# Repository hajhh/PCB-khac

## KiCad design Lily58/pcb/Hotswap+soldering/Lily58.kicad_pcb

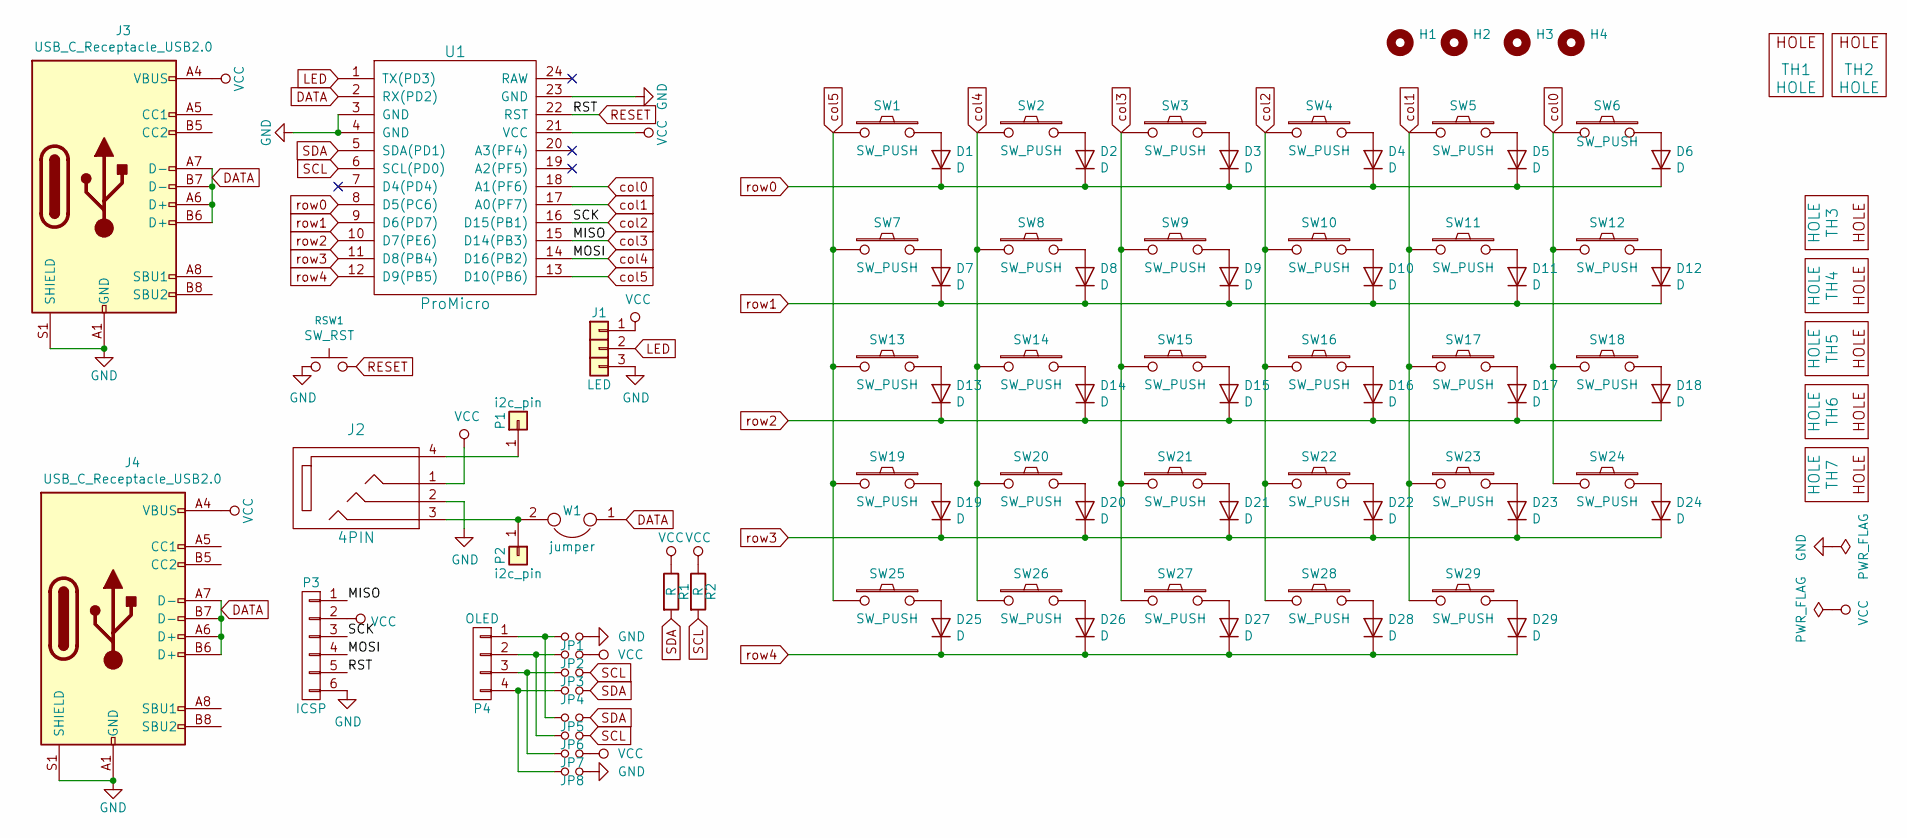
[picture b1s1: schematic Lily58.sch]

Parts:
D1, D2, D3, D4, D5, D6, D7, D8, D9, D10, D11, D12, D13, D14, D15, D16, D17, D18, D19, D20, D21, D22, D23, D24, D25, D26, D27, D28, D29: D; 1N4148_smd
H1, H2: Logo
H3, H4: Logo 2
J1: LED; StripLED
J2: 4PIN; MJ-4PP-9
J3, J4: USB_C_Receptacle_USB2.0; TYPE C
JP1, JP2, JP3, JP4, JP5, JP6, JP7, JP8: Jumper
P1, P2: i2c_pin; 1pin_conn
P3: ICSP
P4: OLED
R1, R2: R; RESISTOR_mini
RSW1: SW_RST; SW_Tactile_SPST_Angled_PTS645Vx39-2LFS
SW1, SW2, SW3, SW4, SW5, SW6, SW7, SW8, SW9, SW10, SW11, SW12, SW13, SW14, SW15, SW16, SW17, SW18, SW19, SW20, SW21, SW22, SW23, SW24, SW25, SW26, SW27, SW28, SW29: SW_PUSH; MX_kien
TH1, TH2: HOLE; HOLE_M2
TH3, TH4, TH5, TH6, TH7: HOLE; HOLE_M2_TH
U1: ProMicro; ProMicro_rev2
W1: jumper; jumper_data

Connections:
DATA: J3.A6 (D+), J3.A7 (D-), J3.B6 (D+), J3.B7 (D-), J4.A6 (D+), J4.A7 (D-), J4.B6 (D+), J4.B7 (D-), U1.2 (RX(PD2)), W1.1
GND: J1.3, J2.2, J3.A1 (GND), J3.A12 (GND), J3.B1 (GND), J3.B12 (GND), J3.S1 (SHIELD), J4.A1 (GND), J4.A12 (GND), J4.B1 (GND), J4.B12 (GND), J4.S1 (SHIELD), JP1.2, JP8.2, P3.6, RSW1.1, U1.3 (GND), U1.4 (GND), U1.23 (GND)
LED: J1.2, U1.1 (TX(PD3))
unnamed: D1.2 (A), SW1.1
unnamed: D2.2 (A), SW2.2
unnamed: D3.2 (A), SW3.2
unnamed: D4.2 (A), SW4.2
unnamed: D5.2 (A), SW5.2
unnamed: D6.2 (A), SW6.2
unnamed: D7.2 (A), SW7.1
unnamed: D8.2 (A), SW8.2
unnamed: D9.2 (A), SW9.2
unnamed: D10.2 (A), SW10.2
unnamed: D11.2 (A), SW11.2
unnamed: D12.2 (A), SW12.2
unnamed: D13.2 (A), SW13.1
unnamed: D14.2 (A), SW14.2
unnamed: D15.2 (A), SW15.2
unnamed: D16.2 (A), SW16.2
unnamed: D17.2 (A), SW17.2
unnamed: D18.2 (A), SW18.2
unnamed: D19.2 (A), SW19.1
unnamed: D20.2 (A), SW20.2
unnamed: D21.2 (A), SW21.2
unnamed: D22.2 (A), SW22.2
unnamed: D23.2 (A), SW23.2
unnamed: D24.2 (A), SW24.2
unnamed: D25.2 (A), SW25.1
unnamed: D26.2 (A), SW26.1
unnamed: D27.2 (A), SW27.2
unnamed: D28.2 (A), SW28.2
unnamed: D29.2 (A), SW29.2
unnamed: J2.3, P2.1, W1.2
unnamed: J2.4, P1.1
unnamed: JP1.1, JP5.1, P4.1
unnamed: JP2.1, JP6.1, P4.2
unnamed: JP3.1, JP7.1, P4.3
unnamed: JP4.1, JP8.1, P4.4
RESET: P3.5, RSW1.2, U1.22 (RST)
SCL: JP3.2, JP6.2, R2.2, U1.6 (SCL(PD0))
SDA: JP4.2, JP5.2, R1.2, U1.5 (SDA(PD1))
VCC: J1.1, J2.1, J3.A4 (VBUS), J3.A9 (VBUS), J3.B4 (VBUS), J3.B9 (VBUS), J4.A4 (VBUS), J4.A9 (VBUS), J4.B4 (VBUS), J4.B9 (VBUS), JP2.2, JP7.2, P3.2, R1.1, R2.1, U1.21 (VCC)
col0: SW6.1, SW12.1, SW18.1, SW24.1, U1.18 (A1(PF6))
col1: SW5.1, SW11.1, SW17.1, SW23.1, SW29.1, U1.17 (A0(PF7))
col2: P3.3, SW4.1, SW10.1, SW16.1, SW22.1, SW28.1, U1.16 (D15(PB1))
col3: P3.1, SW3.1, SW9.1, SW15.1, SW21.1, SW27.1, U1.15 (D14(PB3))
col4: P3.4, SW2.1, SW8.1, SW14.1, SW20.1, SW26.2, U1.14 (D16(PB2))
col5: SW1.2, SW7.2, SW13.2, SW19.2, SW25.2, U1.13 (D10(PB6))
row0: D1.1 (K), D2.1 (K), D3.1 (K), D4.1 (K), D5.1 (K), D6.1 (K), U1.8 (D5(PC6))
row1: D7.1 (K), D8.1 (K), D9.1 (K), D10.1 (K), D11.1 (K), D12.1 (K), U1.9 (D6(PD7))
row2: D13.1 (K), D14.1 (K), D15.1 (K), D16.1 (K), D17.1 (K), D18.1 (K), U1.10 (D7(PE6))
row3: D19.1 (K), D20.1 (K), D21.1 (K), D22.1 (K), D23.1 (K), D24.1 (K), U1.11 (D8(PB4))
row4: D25.1 (K), D26.1 (K), D27.1 (K), D28.1 (K), D29.1 (K), U1.12 (D9(PB5))

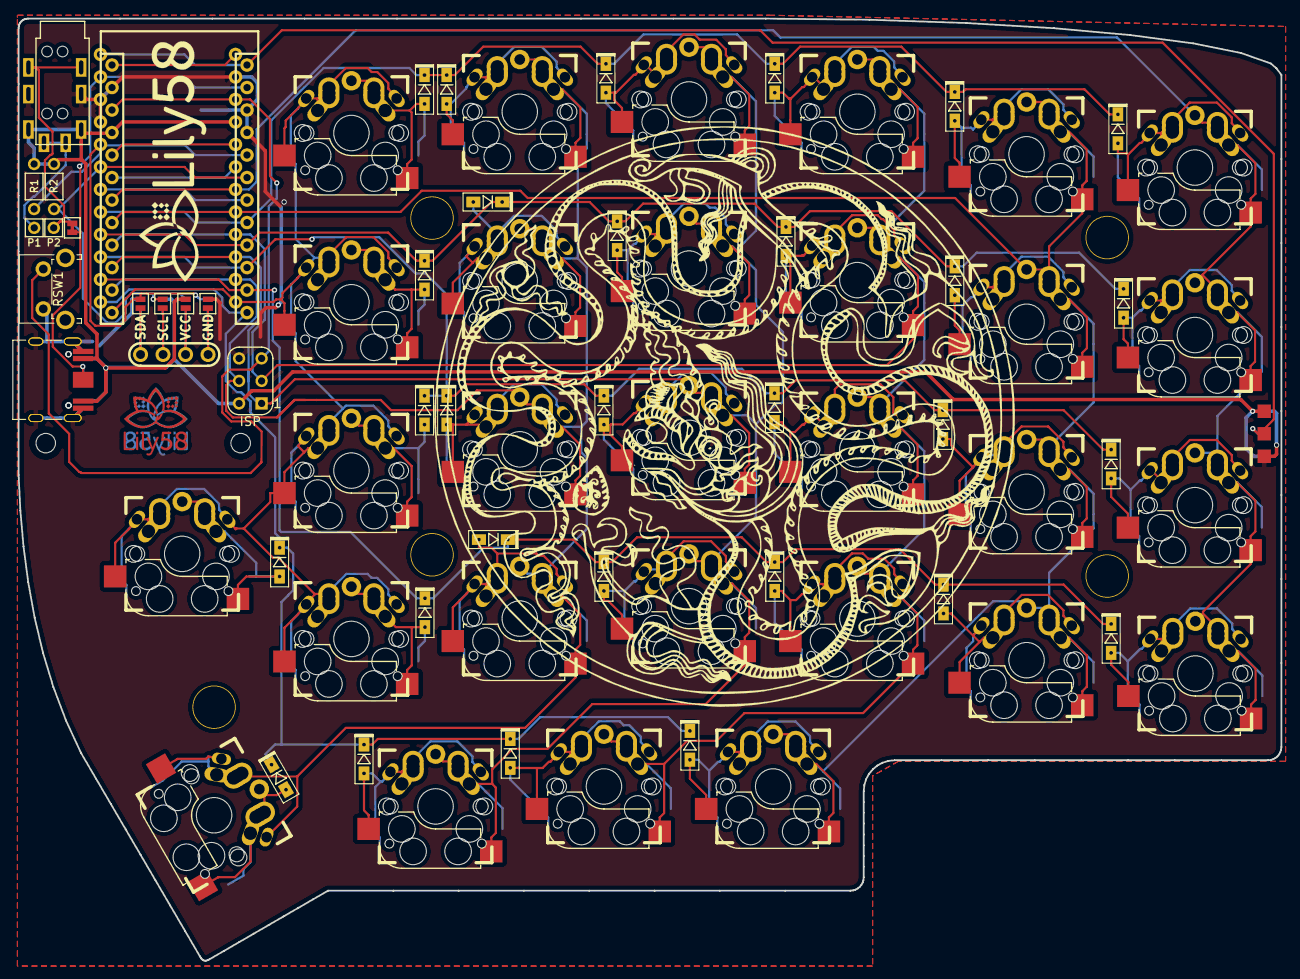
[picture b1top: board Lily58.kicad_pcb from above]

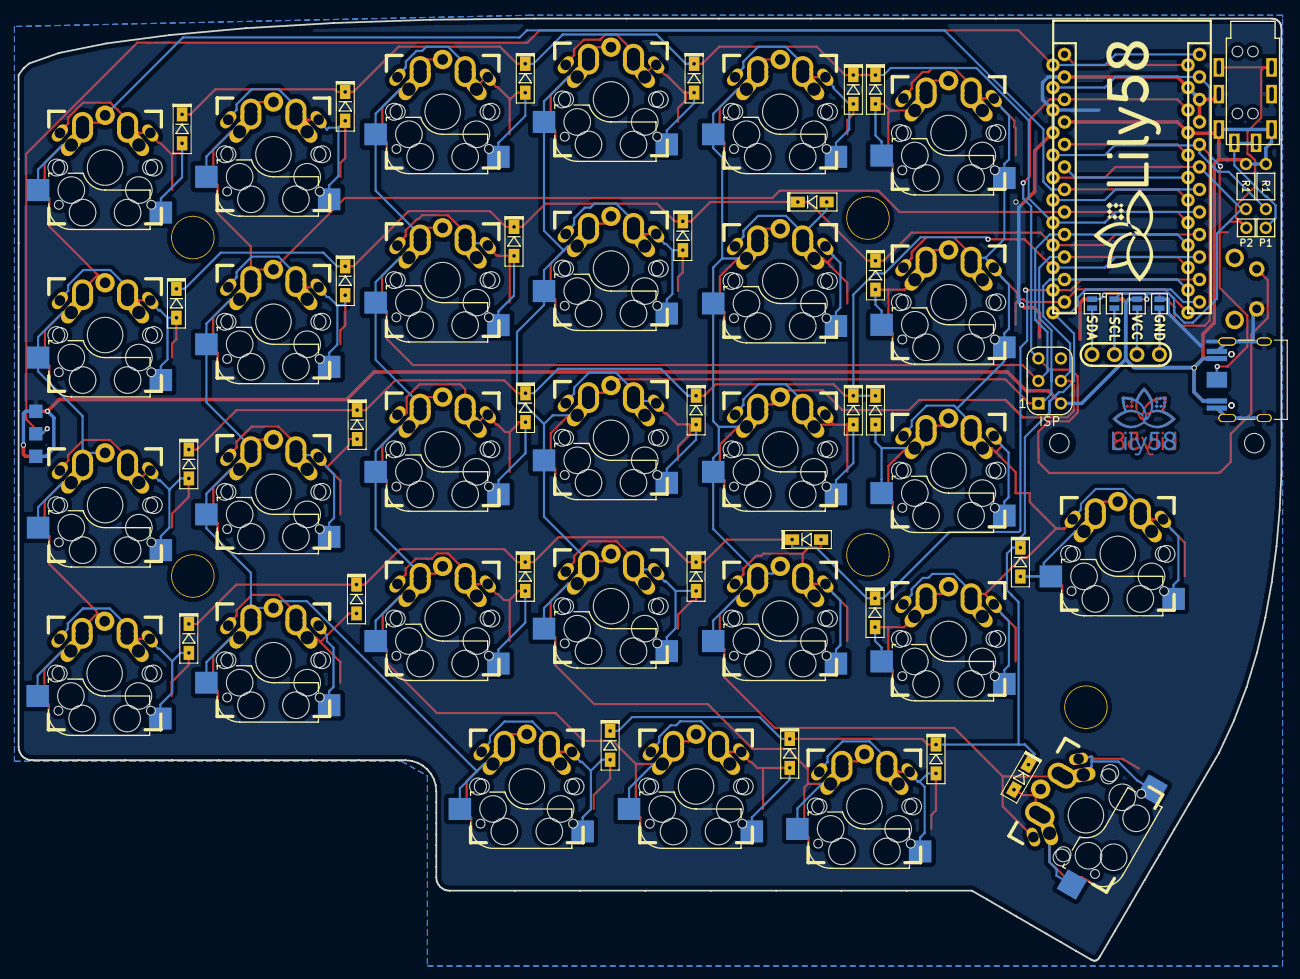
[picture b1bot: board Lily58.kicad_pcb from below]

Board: 2 copper layers, 142.5 x 106.3 mm, 90 parts (7 on the bottom side), 53 nets.

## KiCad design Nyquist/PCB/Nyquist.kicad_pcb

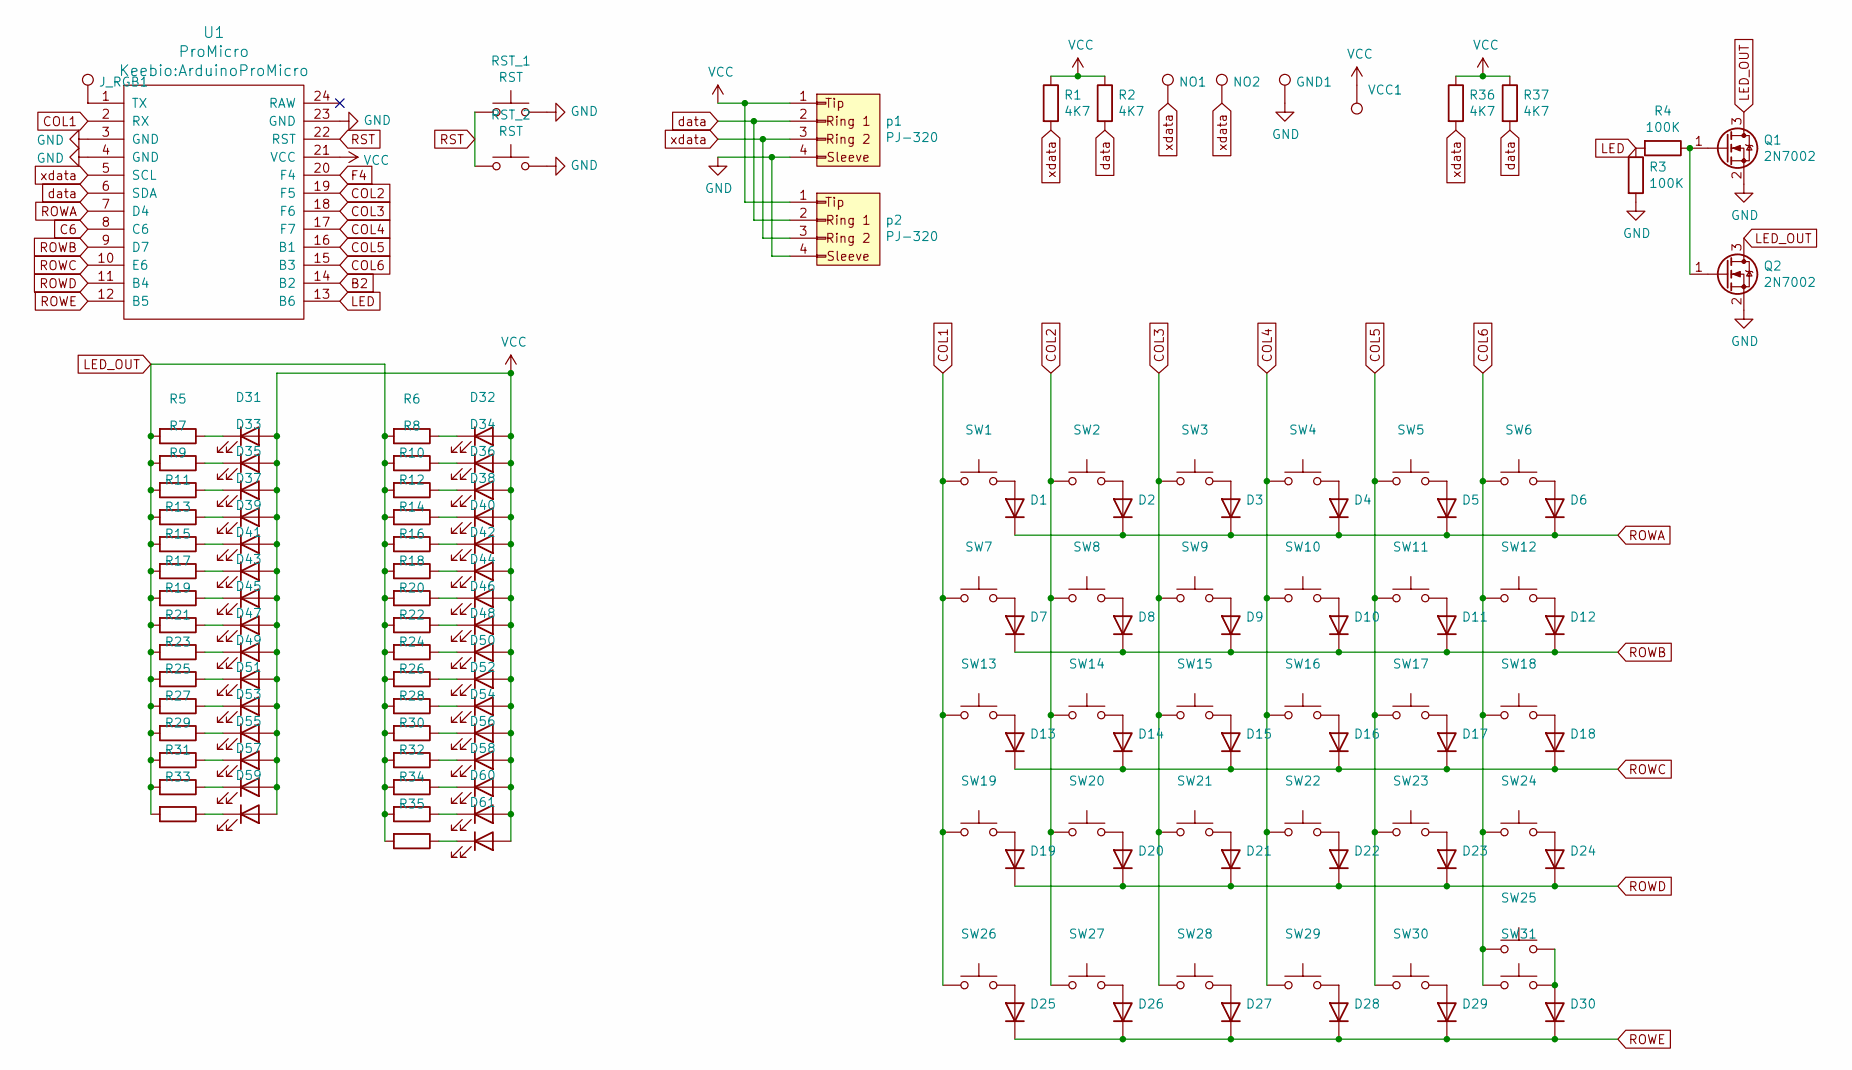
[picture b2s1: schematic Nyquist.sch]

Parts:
D1, D2, D3, D4, D5, D6, D7, D8, D9, D10, D11, D12, D13, D14, D15, D16, D17, D18, D19, D20, D21, D22, D23, D24, D25, D26, D27, D28, D29, D30: Diode
D31, D32, D33, D34, D35, D36, D37, D38, D39, D40, D41, D42, D43, D44, D45, D46, D47, D48, D49, D50, D51, D52, D53, D54, D55, D56, D57, D58, D59, D60, D61: LED_3MM
GND1: TestPoint
J_RGB1: TestPoint
NO1, NO2: TestPoint
Q1, Q2: 2N7002; SOT-23
R1, R2, R36, R37: 4K7; Resistor-Compact
R3, R4: 100K; R
R5, R6, R7, R8, R9, R10, R11, R12, R13, R14, R15, R16, R17, R18, R19, R20, R21, R22, R23, R24, R25, R26, R27, R28, R29, R30, R31, R32, R33, R34, R35: R
RST_1, RST_2: RST
SW1, SW2, SW3, SW4, SW5, SW6, SW7, SW8, SW9, SW10, SW11, SW12, SW13, SW14, SW15, SW16, SW17, SW18, SW19, SW20, SW21, SW22, SW23, SW24, SW25, SW26, SW27, SW28, SW29, SW30: 1u
SW31: 2u
U1: ProMicro; ArduinoProMicro
VCC1: TestPoint
p1, p2: PJ-320; PJ_320

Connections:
B2: U1.14 (B2)
C6: U1.8 (C6)
COL1: SW1.1, SW7.1, SW13.1, SW19.1, SW26.1, U1.2 (RX)
COL2: SW2.1, SW8.1, SW14.1, SW20.1, SW27.1, U1.19 (F5)
COL3: SW3.2, SW9.2, SW15.1, SW21.1, SW28.1, U1.18 (F6)
COL4: SW4.2, SW10.2, SW16.2, SW22.2, SW29.1, U1.17 (F7)
COL5: SW5.2, SW11.2, SW17.2, SW23.2, SW30.1, U1.16 (B1)
COL6: SW6.2, SW12.2, SW18.2, SW24.2, SW25.1, SW31.1, U1.15 (B3)
F4: U1.20 (F4)
GND: GND1.1, Q1.2 (S), Q2.2 (S), R3.2, RST_1.2, RST_2.2, U1.3 (GND), U1.4 (GND), U1.23 (GND), p1.4, p2.4
LED: R3.1, R4.2, U1.13 (B6)
LED_OUT: Q1.3 (D), Q2.3 (D), R5.2, R6.2, R7.2, R8.2, R9.2, R10.2, R11.2, R12.2, R13.2, R14.2, R15.2, R16.2, R17.2, R18.2, R19.2, R20.2, R21.2, R22.2, R23.2, R24.2, R25.2, R26.2, R27.2, R28.2, R29.2, R30.2, R31.2, R32.2, R33.2, R34.2, R35.2
unnamed: D1.1 (A), SW1.2
unnamed: D2.1 (A), SW2.2
unnamed: D3.1 (A), SW3.1
unnamed: D4.1 (A), SW4.1
unnamed: D5.1 (A), SW5.1
unnamed: D6.1 (A), SW6.1
unnamed: D7.1 (A), SW7.2
unnamed: D8.1 (A), SW8.2
unnamed: D9.1 (A), SW9.1
unnamed: D10.1 (A), SW10.1
unnamed: D11.1 (A), SW11.1
unnamed: D12.1 (A), SW12.1
unnamed: D13.1 (A), SW13.2
unnamed: D14.1 (A), SW14.2
unnamed: D15.1 (A), SW15.2
unnamed: D16.1 (A), SW16.1
unnamed: D17.1 (A), SW17.1
unnamed: D18.1 (A), SW18.1
unnamed: D19.1 (A), SW19.2
unnamed: D20.1 (A), SW20.2
unnamed: D21.1 (A), SW21.2
unnamed: D22.1 (A), SW22.1
unnamed: D23.1 (A), SW23.1
unnamed: D24.1 (A), SW24.1
unnamed: D25.1 (A), SW26.2
unnamed: D26.1 (A), SW27.2
unnamed: D27.1 (A), SW28.2
unnamed: D28.1 (A), SW29.2
unnamed: D29.1 (A), SW30.2
unnamed: D30.1 (A), SW25.2, SW31.2
unnamed: D31.1 (K), R5.1
unnamed: D32.1 (K), R6.1
unnamed: D33.1 (K), R7.1
unnamed: D34.1 (K), R8.1
unnamed: D35.1 (K), R9.1
unnamed: D36.1 (K), R10.1
unnamed: D37.1 (K), R11.1
unnamed: D38.1 (K), R12.1
unnamed: D39.1 (K), R13.1
unnamed: D40.1 (K), R14.1
unnamed: D41.1 (K), R15.1
unnamed: D42.1 (K), R16.1
unnamed: D43.1 (K), R17.1
unnamed: D44.1 (K), R18.1
unnamed: D45.1 (K), R19.1
unnamed: D46.1 (K), R20.1
unnamed: D47.1 (K), R21.1
unnamed: D48.1 (K), R22.1
unnamed: D49.1 (K), R23.1
unnamed: D50.1 (K), R24.1
unnamed: D51.1 (K), R25.1
unnamed: D52.1 (K), R26.1
unnamed: D53.1 (K), R27.1
unnamed: D54.1 (K), R28.1
unnamed: D55.1 (K), R29.1
unnamed: D56.1 (K), R30.1
unnamed: D57.1 (K), R31.1
unnamed: D58.1 (K), R32.1
unnamed: D59.1 (K), R33.1
unnamed: D60.1 (K), R34.1
unnamed: D61.1 (K), R35.1
unnamed: J_RGB1.1, U1.1 (TX)
unnamed: Q1.1 (G), Q2.1 (G), R4.1
ROWA: D1.2 (K), D2.2 (K), D3.2 (K), D4.2 (K), D5.2 (K), D6.2 (K), U1.7 (D4)
ROWB: D7.2 (K), D8.2 (K), D9.2 (K), D10.2 (K), D11.2 (K), D12.2 (K), U1.9 (D7)
ROWC: D13.2 (K), D14.2 (K), D15.2 (K), D16.2 (K), D17.2 (K), D18.2 (K), U1.10 (E6)
ROWD: D19.2 (K), D20.2 (K), D21.2 (K), D22.2 (K), D23.2 (K), D24.2 (K), U1.11 (B4)
ROWE: D25.2 (K), D26.2 (K), D27.2 (K), D28.2 (K), D29.2 (K), D30.2 (K), U1.12 (B5)
RST: RST_1.1, RST_2.1, U1.22 (RST)
VCC: D31.2 (A), D32.2 (A), D33.2 (A), D34.2 (A), D35.2 (A), D36.2 (A), D37.2 (A), D38.2 (A), D39.2 (A), D40.2 (A), D41.2 (A), D42.2 (A), D43.2 (A), D44.2 (A), D45.2 (A), D46.2 (A), D47.2 (A), D48.2 (A), D49.2 (A), D50.2 (A), D51.2 (A), D52.2 (A), D53.2 (A), D54.2 (A), D55.2 (A), D56.2 (A), D57.2 (A), D58.2 (A), D59.2 (A), D60.2 (A), D61.2 (A), R1.1, R2.1, R36.1, R37.1, U1.21 (VCC), VCC1.1, p1.1, p2.1
data: R2.2, R37.2, U1.6 (SDA), p1.2, p2.2
xdata: NO1.1, NO2.1, R1.2, R36.2, U1.5 (SCL), p1.3, p2.3

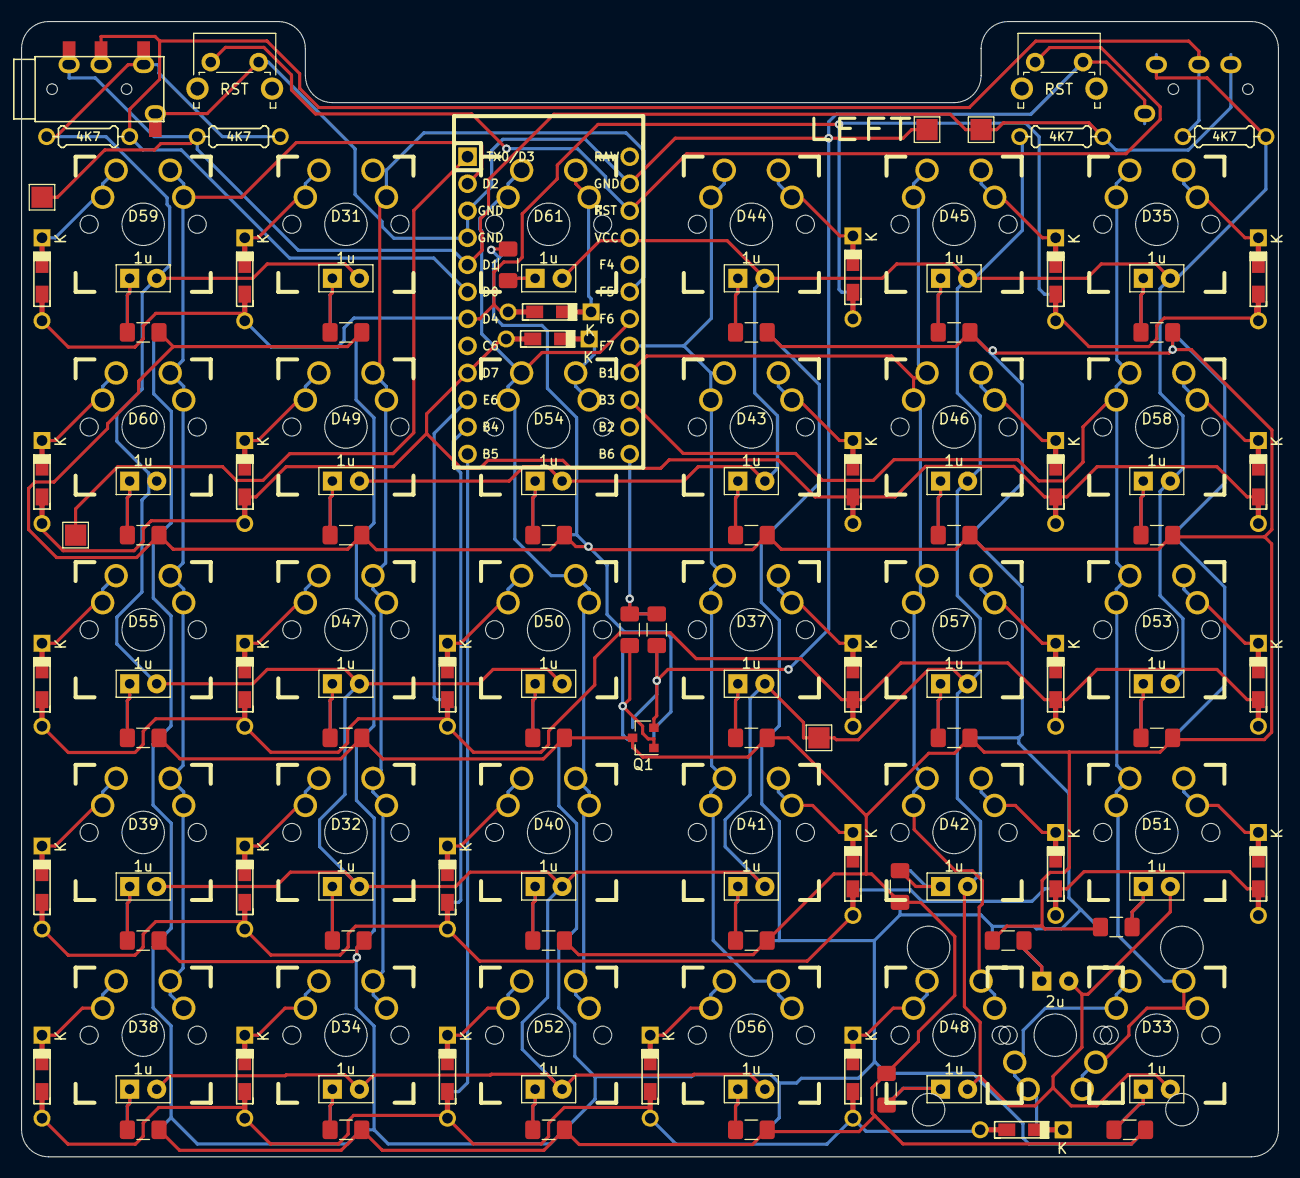
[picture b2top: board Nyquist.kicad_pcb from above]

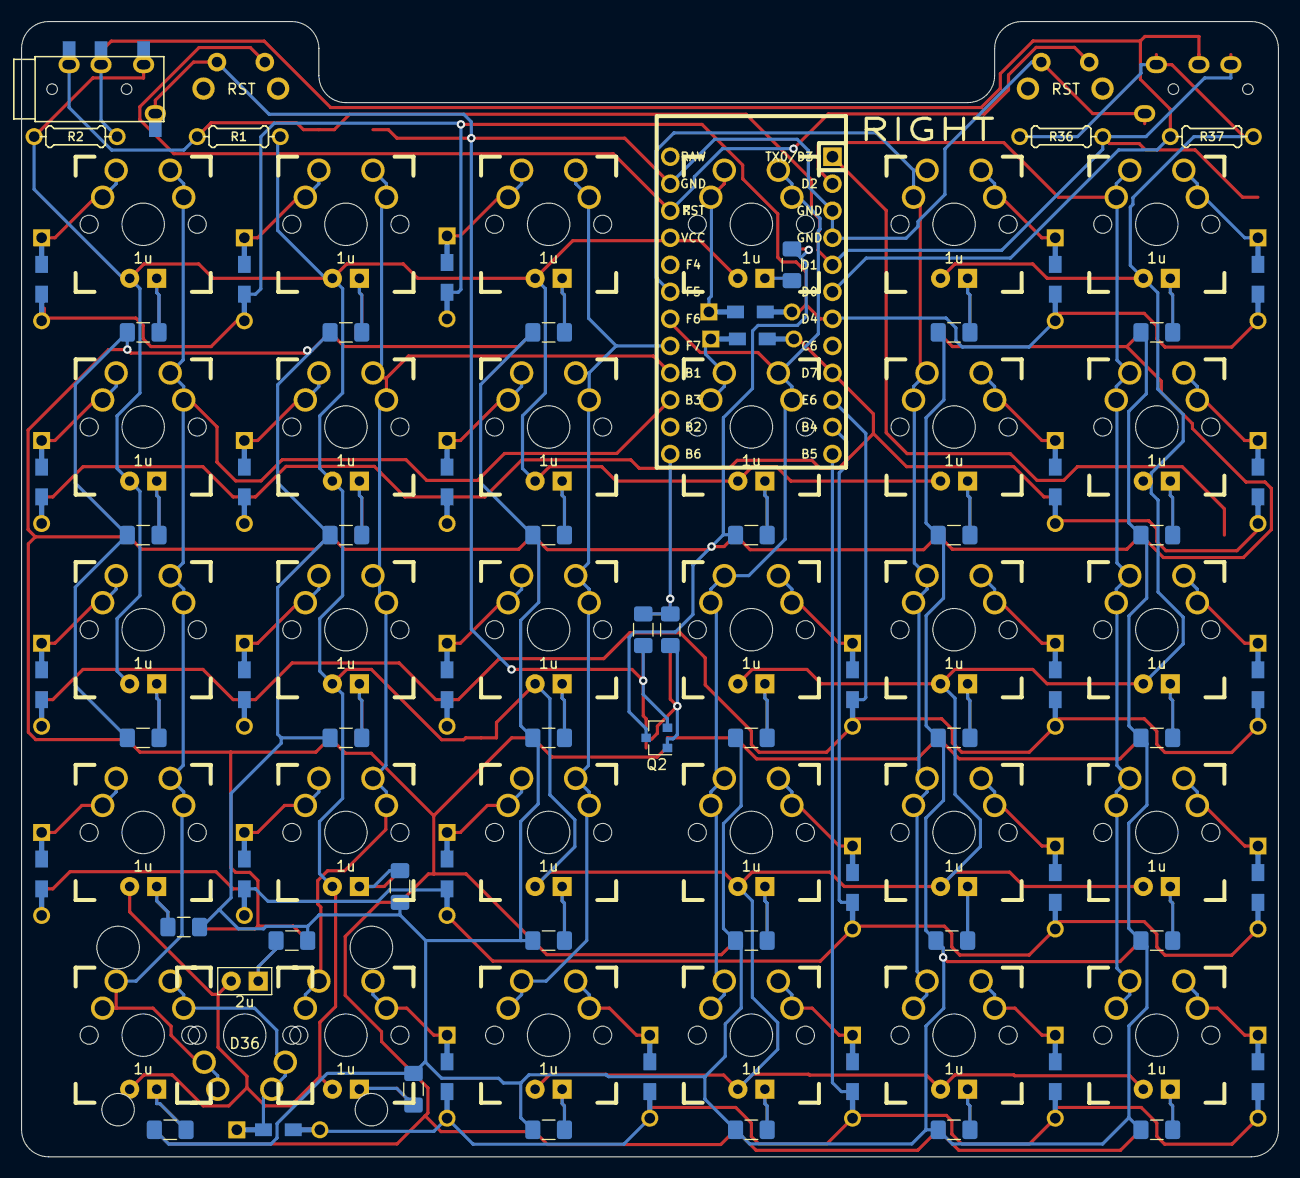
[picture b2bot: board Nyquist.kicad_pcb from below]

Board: 2 copper layers, 118.1 x 106.7 mm, 141 parts (3 on the bottom side), 81 nets.

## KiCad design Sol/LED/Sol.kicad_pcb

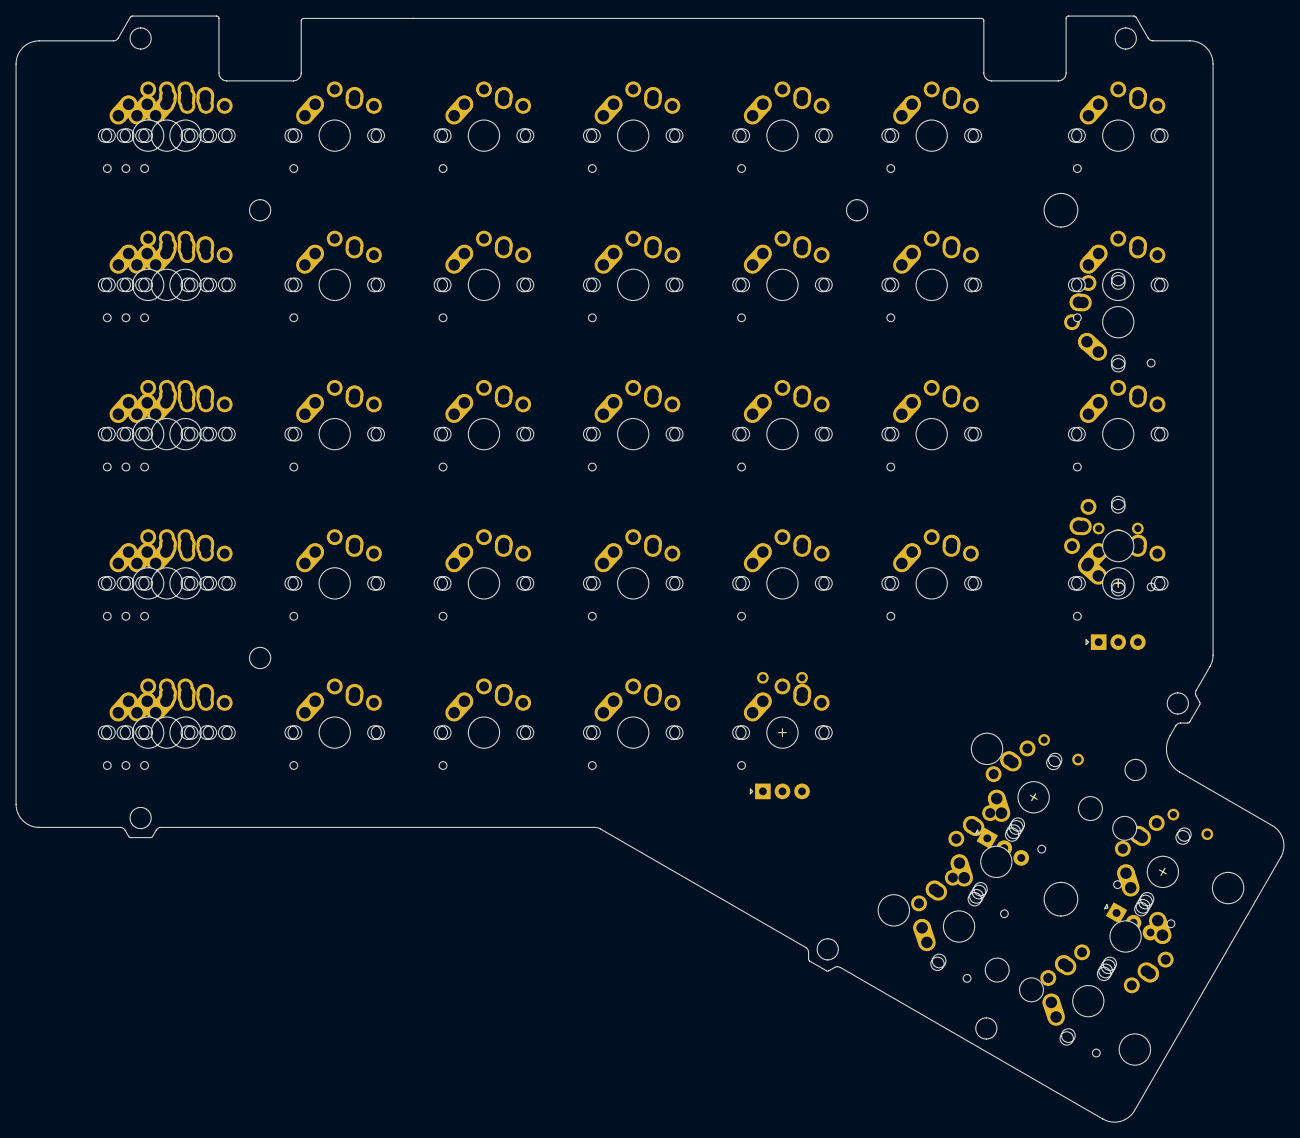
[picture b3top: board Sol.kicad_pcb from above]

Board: 2 copper layers, 161.8 x 141.2 mm, 48 parts (1 on the bottom side), 3 nets, no tracks yet.

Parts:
H1, H2: Stab
SW1, SW8, SW15, SW22, SW29: MX
SW2, SW3, SW4, SW5, SW6, SW7, SW9, SW10, SW11, SW12, SW13, SW14, SW16, SW17, SW18, SW19, SW20, SW21, SW23, SW24, SW25, SW26, SW27, SW28, SW30, SW31, SW32, SW33, SW34, SW35, SW36, SW37, SW38, SW39, SW40, SW41: MX-1U-NoLED
SW42, SW43, SW44, SW45: Econder
U1: ATmega32U4-MU; QFN-44-1EP_7x7mm_P0.5mm_EP5.2x5.2mm

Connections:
unnamed: U1.14, U1.34
unnamed: U1.15, U1.23, U1.35, U1.43, U1.45
unnamed: U1.24, U1.44

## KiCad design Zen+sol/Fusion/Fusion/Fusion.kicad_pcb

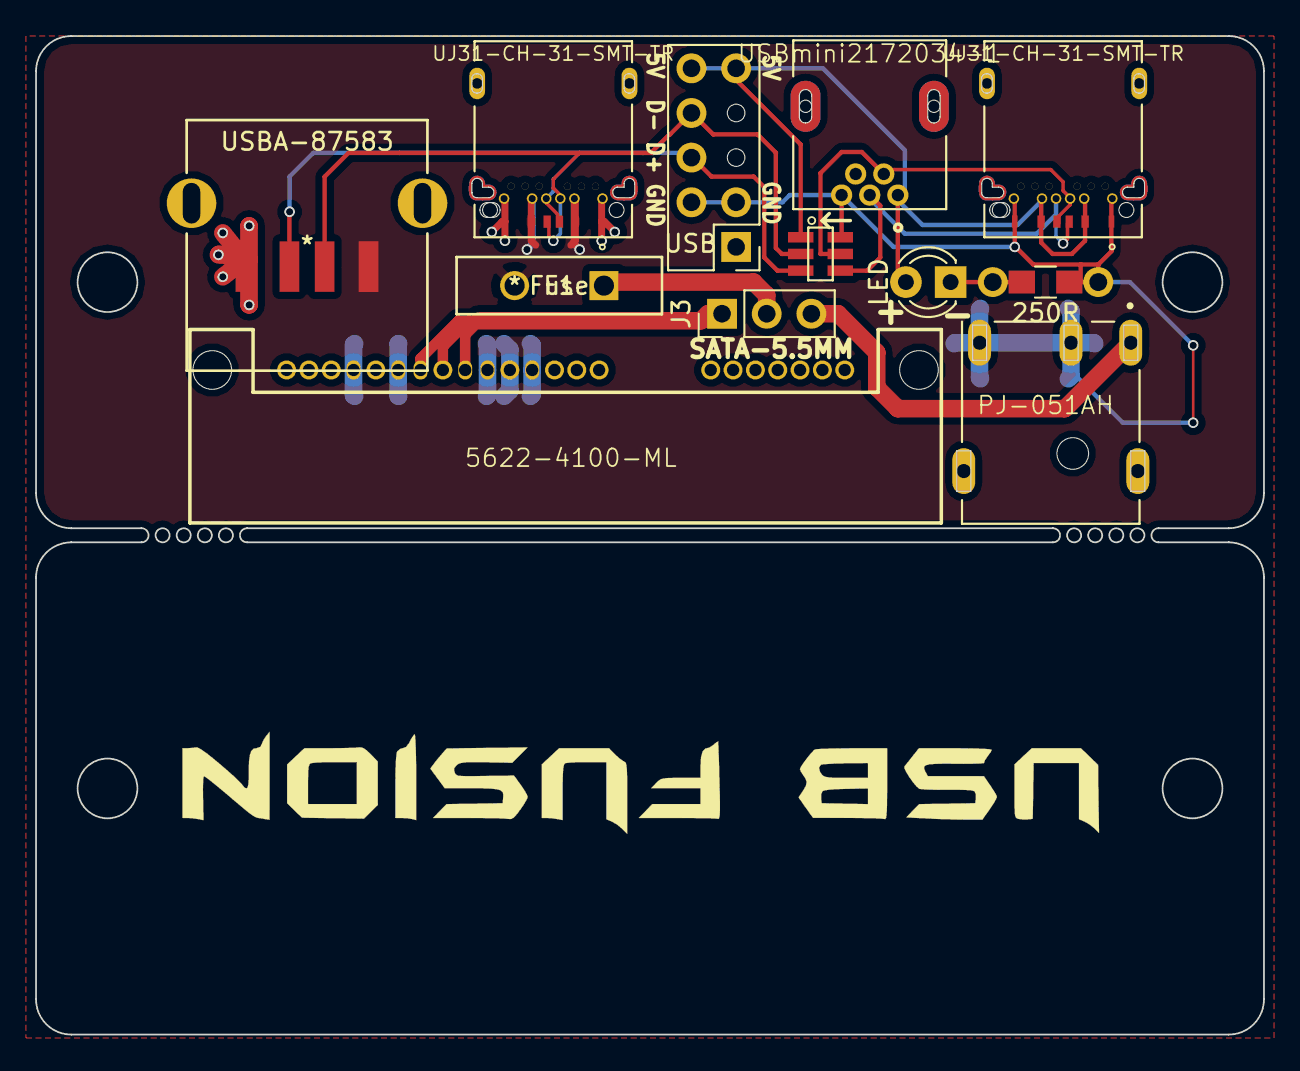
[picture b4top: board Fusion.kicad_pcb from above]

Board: 2 copper layers, 69.8 x 56.8 mm, 12 parts (0 on the bottom side), 11 nets.

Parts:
D1: LED; LED_D3.0mm
F1: Fuse; RUEF300
J1: USBmini2172034-1; TE_2172034-1
J2, J5: UJ31-CH-31-SMT-TR; CUI_UJ31-CH-31-SMT-TR
J3: Conn_01x03_Male; Pin_Header_Straight_1x03_Pitch2.54mm
J4: USBA-87583; 87583-2010BLF
J6: PJ-051AH; CUI_PJ-051AH
P1: 5622-4100-ML; 3M_5622-4100-ML
R1: 250R; R_0805_HandSoldering
U1: STF202-22T1G
USB: 2x05_2.54mm; Pin_Header_Straight_2x05_Pitch2.54mm

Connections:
+5V: F1.2, J2.A4, J2.A9, J2.B4, J2.B9, J4.1
/D+: J1.3, J2.A6, J2.B6, J4.3, J5.A6, J5.B6, U1.3, U1.4, USB.6
/D-: J1.2, J2.A7, J2.B7, J4.2, J5.A7, J5.B7, U1.2, U1.5
/USBGND: J1.5, J1.SH1, J1.SH2, J5.A1, J5.A12, J5.B1, J5.B12, J5.EXPB, R1.2, U1.6
/USBVCC: D1.2, J1.1, J5.A4, J5.A9, J5.B4, J5.B9, U1.1, USB.9
GND: J2.A1, J2.A12, J2.B1, J2.B12, J2.EXPB, J4.4, J6.2, J6.3, P1.P4, P1.P5, P1.P6, P1.P10, P1.P12
unnamed: D1.1, R1.1
unnamed: F1.1, J3.2
unnamed: J3.1, P1.P7, P1.P8, P1.P9
unnamed: J3.3, J6.1
unnamed: J6.5, J6.6

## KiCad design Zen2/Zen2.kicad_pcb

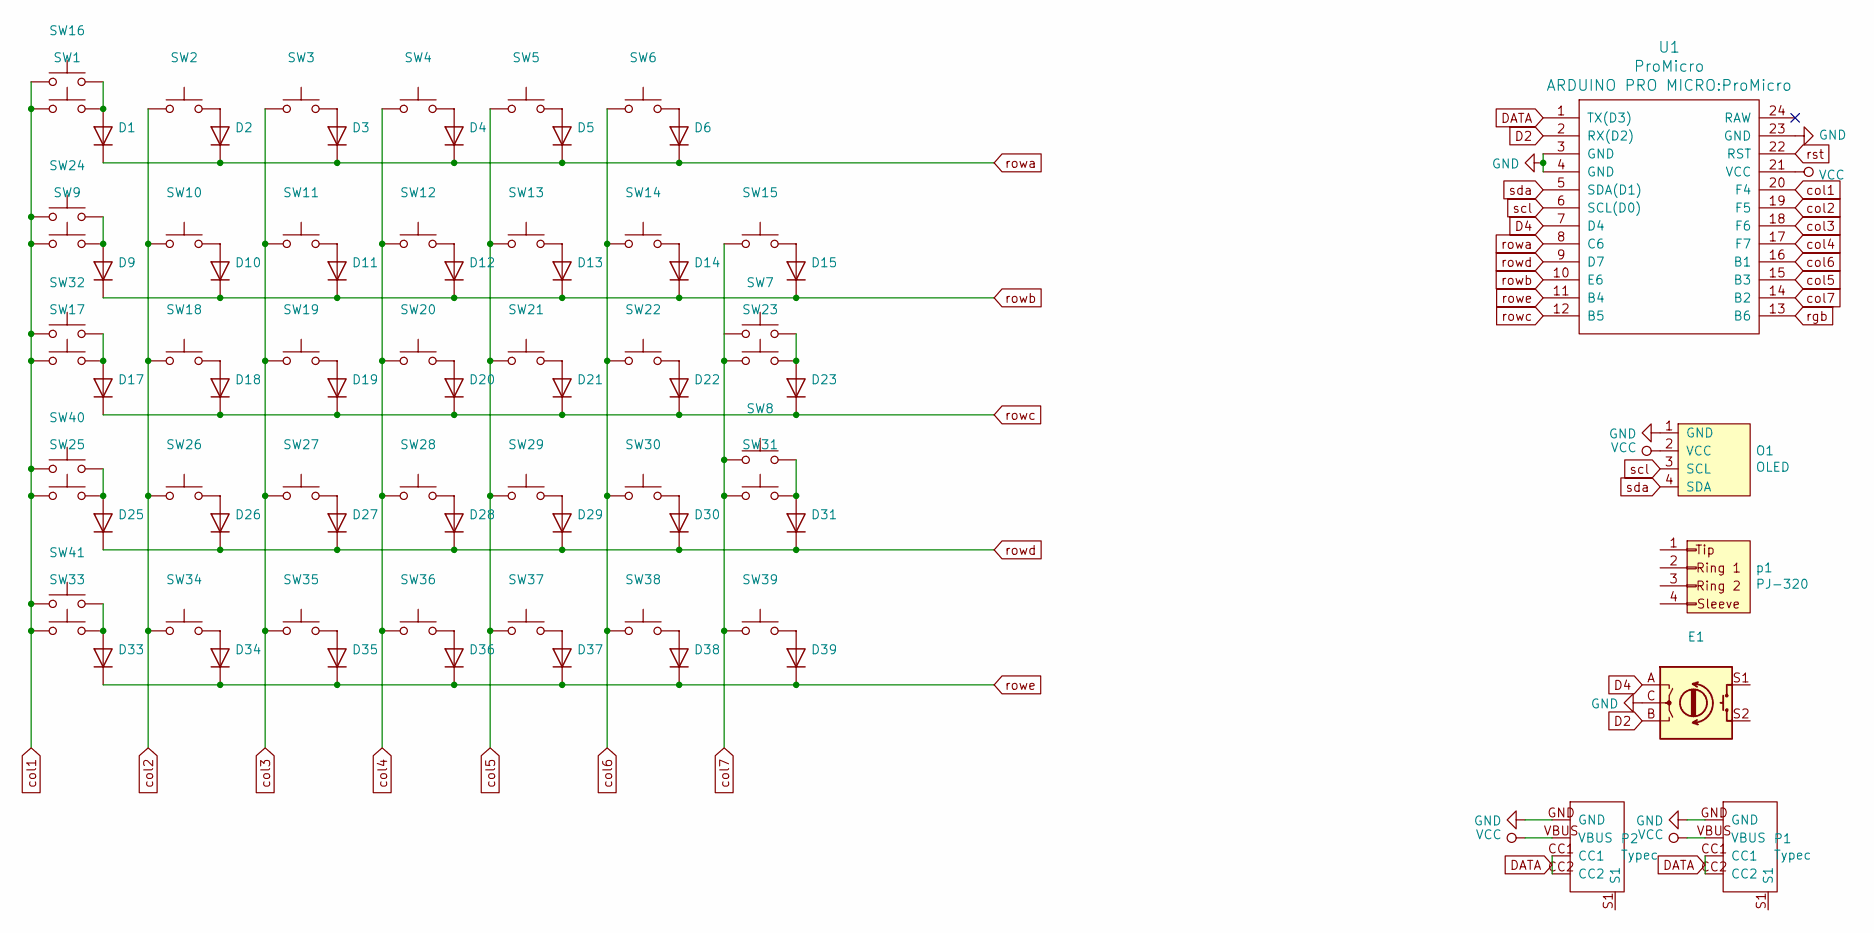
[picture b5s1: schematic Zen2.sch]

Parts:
D1, D2, D3, D4, D5, D6, D9, D10, D11, D12, D13, D14, D15, D17, D18, D19, D20, D21, D22, D23, D25, D26, D27, D28, D29, D30, D31, D33, D34, D35, D36, D37, D38, D39: 1N4148_smd
E1: ECODER
O1: OLED
P1, P2: Typec; Type_c_6pin
SW1, SW9, SW17, SW25, SW33: 1.5u
SW2, SW3, SW4, SW5, SW6, SW10, SW11, SW12, SW13, SW14, SW15, SW16, SW18, SW19, SW20, SW21, SW22, SW23, SW24, SW26, SW27, SW28, SW29, SW30, SW31, SW32, SW34, SW35, SW36, SW37, SW38, SW39, SW40, SW41: 1u
SW7, SW8: 2u
U1: ProMicro
p1: PJ-320; PJ-320A

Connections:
D2: E1.B, U1.2 (RX(D2))
D4: E1.A, U1.7 (D4)
DATA: P1.CC1, P1.CC2, P2.CC1, P2.CC2, U1.1 (TX(D3))
GND: E1.C, O1.1 (GND), P1.GND, P2.GND, U1.3 (GND), U1.4 (GND), U1.23 (GND)
unnamed: D1.2 (A), SW1.2, SW16.1
unnamed: D2.2 (A), SW2.2
unnamed: D3.2 (A), SW3.2
unnamed: D4.2 (A), SW4.2
unnamed: D5.2 (A), SW5.2
unnamed: D6.2 (A), SW6.2
unnamed: D9.2 (A), SW9.2, SW24.1
unnamed: D10.2 (A), SW10.2
unnamed: D11.2 (A), SW11.2
unnamed: D12.2 (A), SW12.2
unnamed: D13.2 (A), SW13.2
unnamed: D14.2 (A), SW14.2
unnamed: D15.2 (A), SW15.2
unnamed: D17.2 (A), SW17.2, SW32.1
unnamed: D18.2 (A), SW18.2
unnamed: D19.2 (A), SW19.2
unnamed: D20.2 (A), SW20.2
unnamed: D21.2 (A), SW21.2
unnamed: D22.2 (A), SW22.2
unnamed: D23.2 (A), SW7.2, SW23.2
unnamed: D25.2 (A), SW25.2, SW40.1
unnamed: D26.2 (A), SW26.2
unnamed: D27.2 (A), SW27.2
unnamed: D28.2 (A), SW28.2
unnamed: D29.2 (A), SW29.2
unnamed: D30.2 (A), SW30.2
unnamed: D31.2 (A), SW8.2, SW31.2
unnamed: D33.2 (A), SW33.2, SW41.1
unnamed: D34.2 (A), SW34.2
unnamed: D35.2 (A), SW35.2
unnamed: D36.2 (A), SW36.2
unnamed: D37.2 (A), SW37.2
unnamed: D38.2 (A), SW38.2
unnamed: D39.2 (A), SW39.2
VCC: O1.2 (VCC), P1.VBUS, P2.VBUS, U1.21 (VCC)
col1: SW1.1, SW9.1, SW16.2, SW17.1, SW24.2, SW25.1, SW32.2, SW33.1, SW40.2, SW41.2, U1.20 (F4)
col2: SW2.1, SW10.1, SW18.1, SW26.1, SW34.1, U1.19 (F5)
col3: SW3.1, SW11.1, SW19.1, SW27.1, SW35.1, U1.18 (F6)
col4: SW4.1, SW12.1, SW20.1, SW28.1, SW36.1, U1.17 (F7)
col5: SW5.1, SW13.1, SW21.1, SW29.1, SW37.1, U1.15 (B3)
col6: SW6.1, SW14.1, SW22.1, SW30.1, SW38.1, U1.16 (B1)
col7: SW8.1, SW15.1, SW23.1, SW31.1, SW39.1, U1.14 (B2)
rgb: U1.13 (B6)
rowa: D1.1 (K), D2.1 (K), D3.1 (K), D4.1 (K), D5.1 (K), D6.1 (K), U1.8 (C6)
rowb: D9.1 (K), D10.1 (K), D11.1 (K), D12.1 (K), D13.1 (K), D14.1 (K), D15.1 (K), U1.10 (E6)
rowc: D17.1 (K), D18.1 (K), D19.1 (K), D20.1 (K), D21.1 (K), D22.1 (K), D23.1 (K), U1.12 (B5)
rowd: D25.1 (K), D26.1 (K), D27.1 (K), D28.1 (K), D29.1 (K), D30.1 (K), D31.1 (K), U1.9 (D7)
rowe: D33.1 (K), D34.1 (K), D35.1 (K), D36.1 (K), D37.1 (K), D38.1 (K), D39.1 (K), U1.11 (B4)
rst: U1.22 (RST)
scl: O1.3 (SCL), U1.6 (SCL(D0))
sda: O1.4 (SDA), U1.5 (SDA(D1))

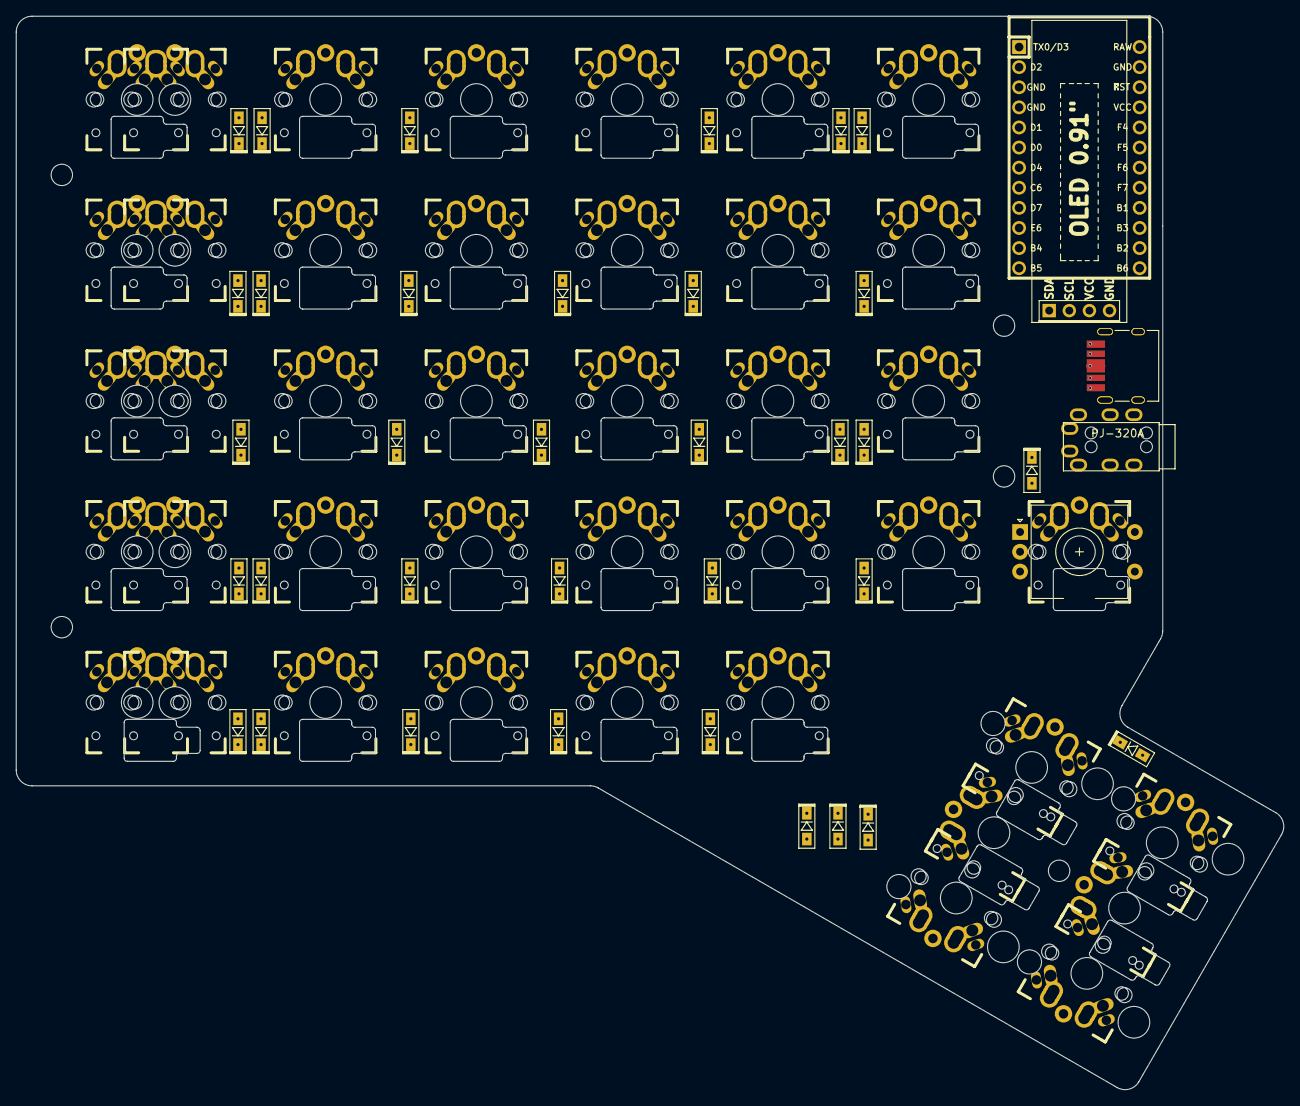
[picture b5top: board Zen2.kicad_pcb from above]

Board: 2 copper layers, 160.2 x 135.6 mm, 81 parts (1 on the bottom side), 53 nets.

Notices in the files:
parts and their libraries:
Copyright 2016 Accelerated Designs. All rights reserved.
